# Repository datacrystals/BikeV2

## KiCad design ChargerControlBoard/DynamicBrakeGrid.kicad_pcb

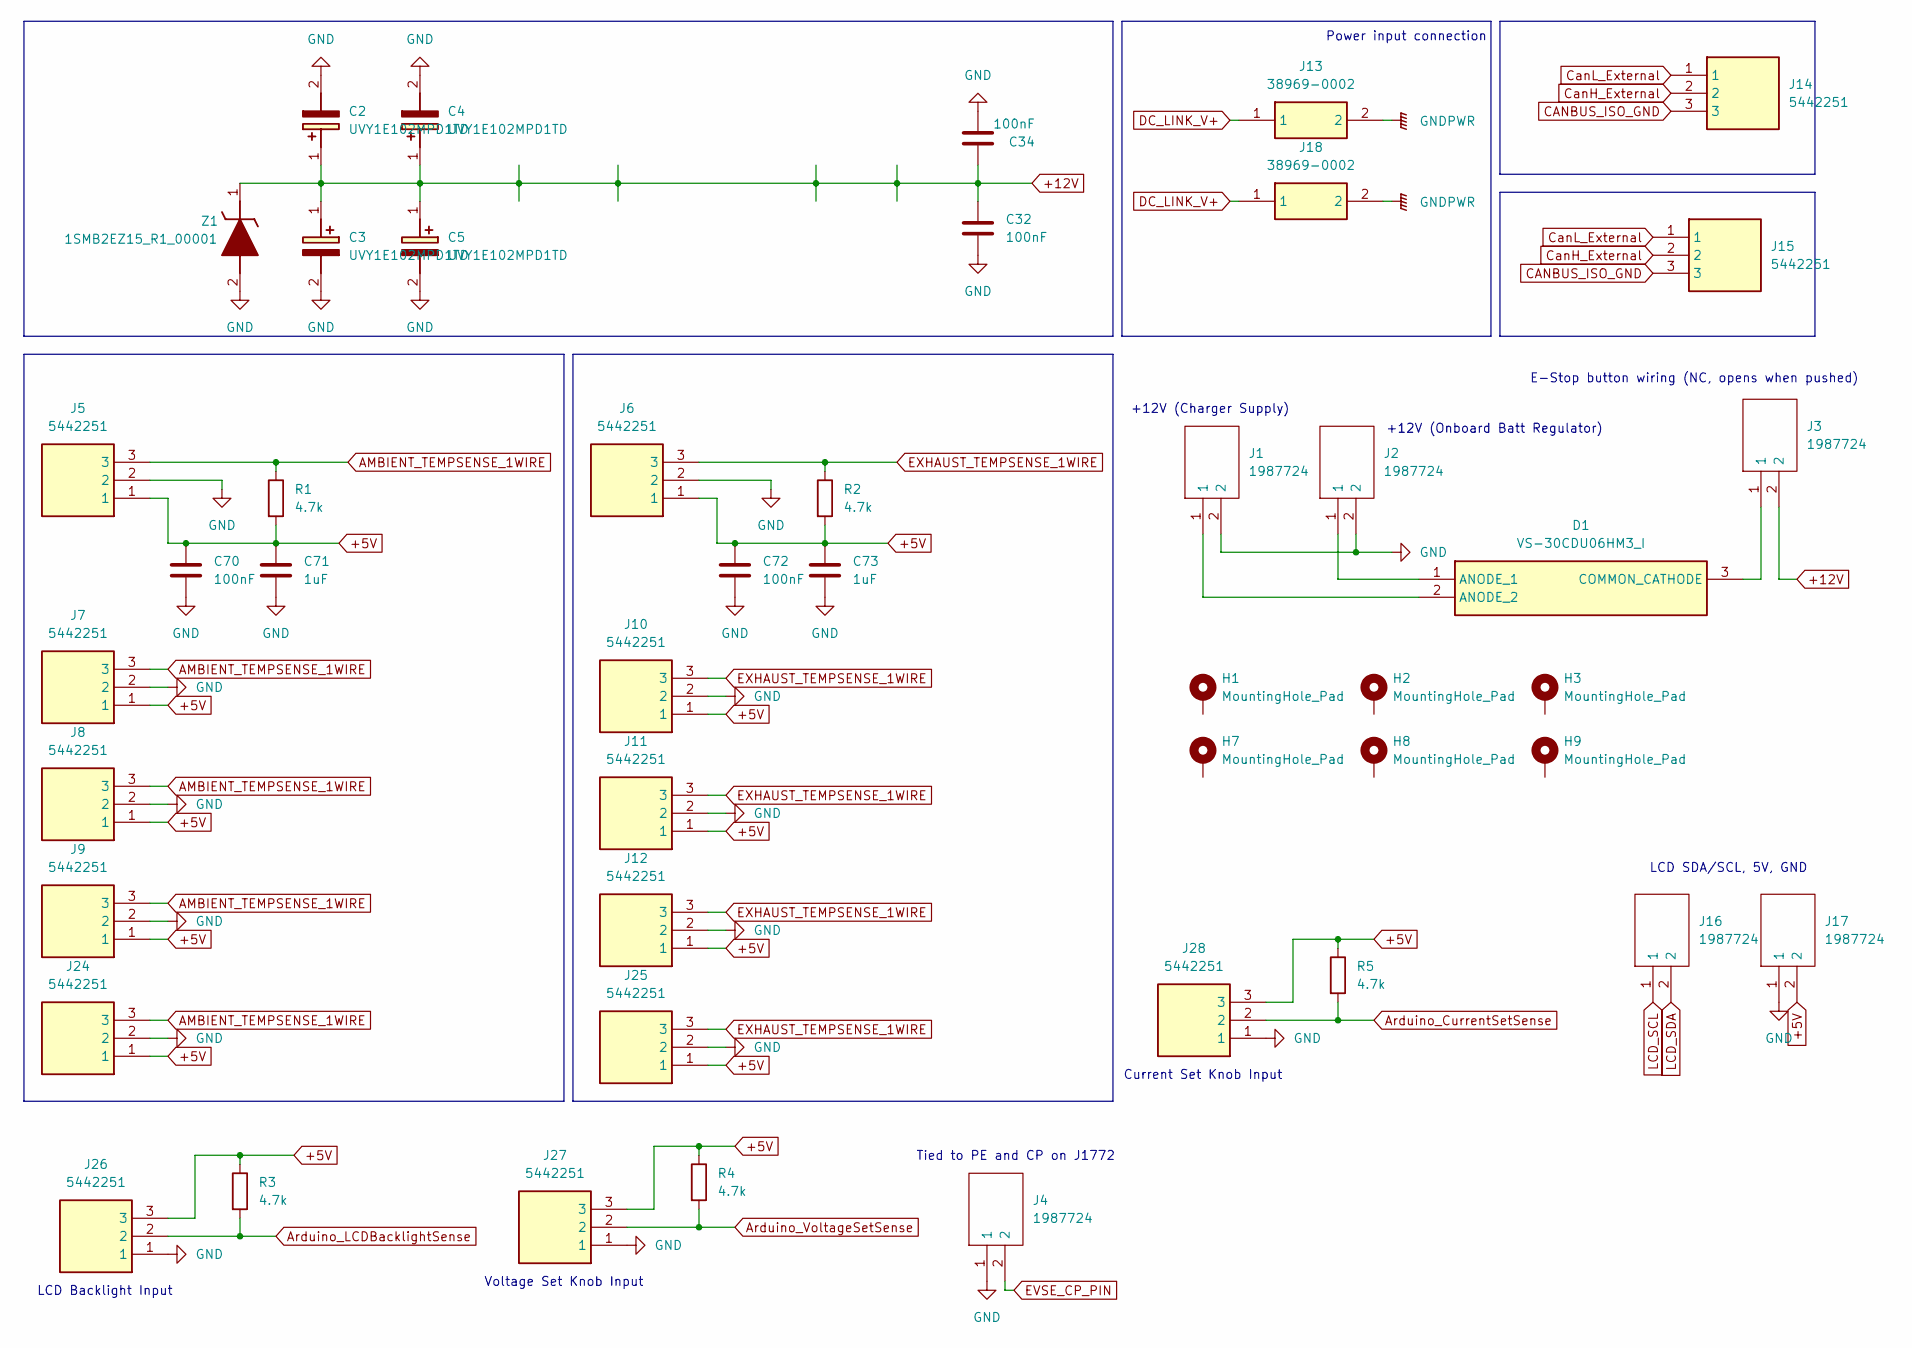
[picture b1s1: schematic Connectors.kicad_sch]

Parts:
C2, C3, C4, C5: UVY1E102MPD1TD; CAPPRD500W60D1025H1750; Mouser Part Number 647-UVY1E102MPD1TD
C32, C34, C70, C72: 100nF; C_1210_3225Metric_Pad1.33x2.70mm_HandSolder
C71, C73: 1uF; C_1210_3225Metric_Pad1.33x2.70mm_HandSolder
D1: VS-30CDU06HM3_I; VS30CDU06HM3I; Mouser Part Number 78-VS-30CDU06HM3I
H1, H2, H3, H7, H8, H9: MountingHole_Pad; MountingHole_5.3mm_M5_ISO7380_Pad
J1, J2, J3, J4, J16, J17: 1987724; Mouser Part Number 651-1987724
J5, J6, J7, J8, J9, J10, J11, J12, J14, J15, J24, J25, J26, J27, J28: 5442251; Mouser Part Number 651-5442251
J13, J18: 38969-0002; 389690002; Mouser Part Number 538-38969-0002
R1, R2, R3, R4, R5: 4.7k; R_1210_3225Metric_Pad1.30x2.65mm_HandSolder
Z1: 1SMB2EZ15_R1_00001; Mouser Part Number 241-1SMB2EZ15R100001

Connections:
+5V: C70.1, C71.1, C72.1, C73.1, J5.1, J6.1, J7.1, J8.1, J9.1, J10.1, J11.1, J12.1, J17.2, J24.1, J25.1, J26.3, J27.3, J28.3, R1.2, R2.2, R3.1, R4.1, R5.1; also elsewhere on the board
+12V: C2.1 (+), C3.1 (+), C4.1 (+), C5.1 (+), C32.1, C34.1, J3.2, Z1.1 (K); also elsewhere on the board
AMBIENT_TEMPSENSE_1WIRE: J5.3, J7.3, J8.3, J9.3, J24.3, R1.1; also elsewhere on the board
Arduino_CurrentSetSense: J28.2, R5.2; also elsewhere on the board
Arduino_LCDBacklightSense: J26.2, R3.2; also elsewhere on the board
Arduino_VoltageSetSense: J27.2, R4.2; also elsewhere on the board
CANBUS_ISO_GND: J14.3, J15.3; also elsewhere on the board
CanH_External: J14.2, J15.2; also elsewhere on the board
CanL_External: J14.1, J15.1; also elsewhere on the board
DC_LINK_V+: J13.1, J18.1; also elsewhere on the board
EVSE_CP_PIN: J4.2; also elsewhere on the board
EXHAUST_TEMPSENSE_1WIRE: J6.3, J10.3, J11.3, J12.3, J25.3, R2.1; also elsewhere on the board
GND: C2.2 (-), C3.2 (-), C4.2 (-), C5.2 (-), C32.2, C34.2, C70.2, C71.2, C72.2, C73.2, J1.2, J2.2, J4.1, J5.2, J6.2, J7.2, J8.2, J9.2, J10.2, J11.2, J12.2, J13.2, J17.1, J18.2, J24.2, J25.2, J26.1, J27.1, J28.1, Z1.2 (A); also elsewhere on the board
LCD_SCL: J16.1; also elsewhere on the board
LCD_SDA: J16.2; also elsewhere on the board
unnamed: D1.1 (ANODE_1), J2.1
unnamed: D1.2 (ANODE_2), J1.1
unnamed: D1.3 (COMMON_CATHODE), J3.1

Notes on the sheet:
E-Stop button wiring (NC, opens when pushed)
LCD Backlight Input
Voltage Set Knob Input
LCD SDA/SCL, 5V, GND
+12V (Onboard Batt Regulator)
+12V (Charger Supply)
Tied to PE and CP on J1772
Current Set Knob Input
Power input connection

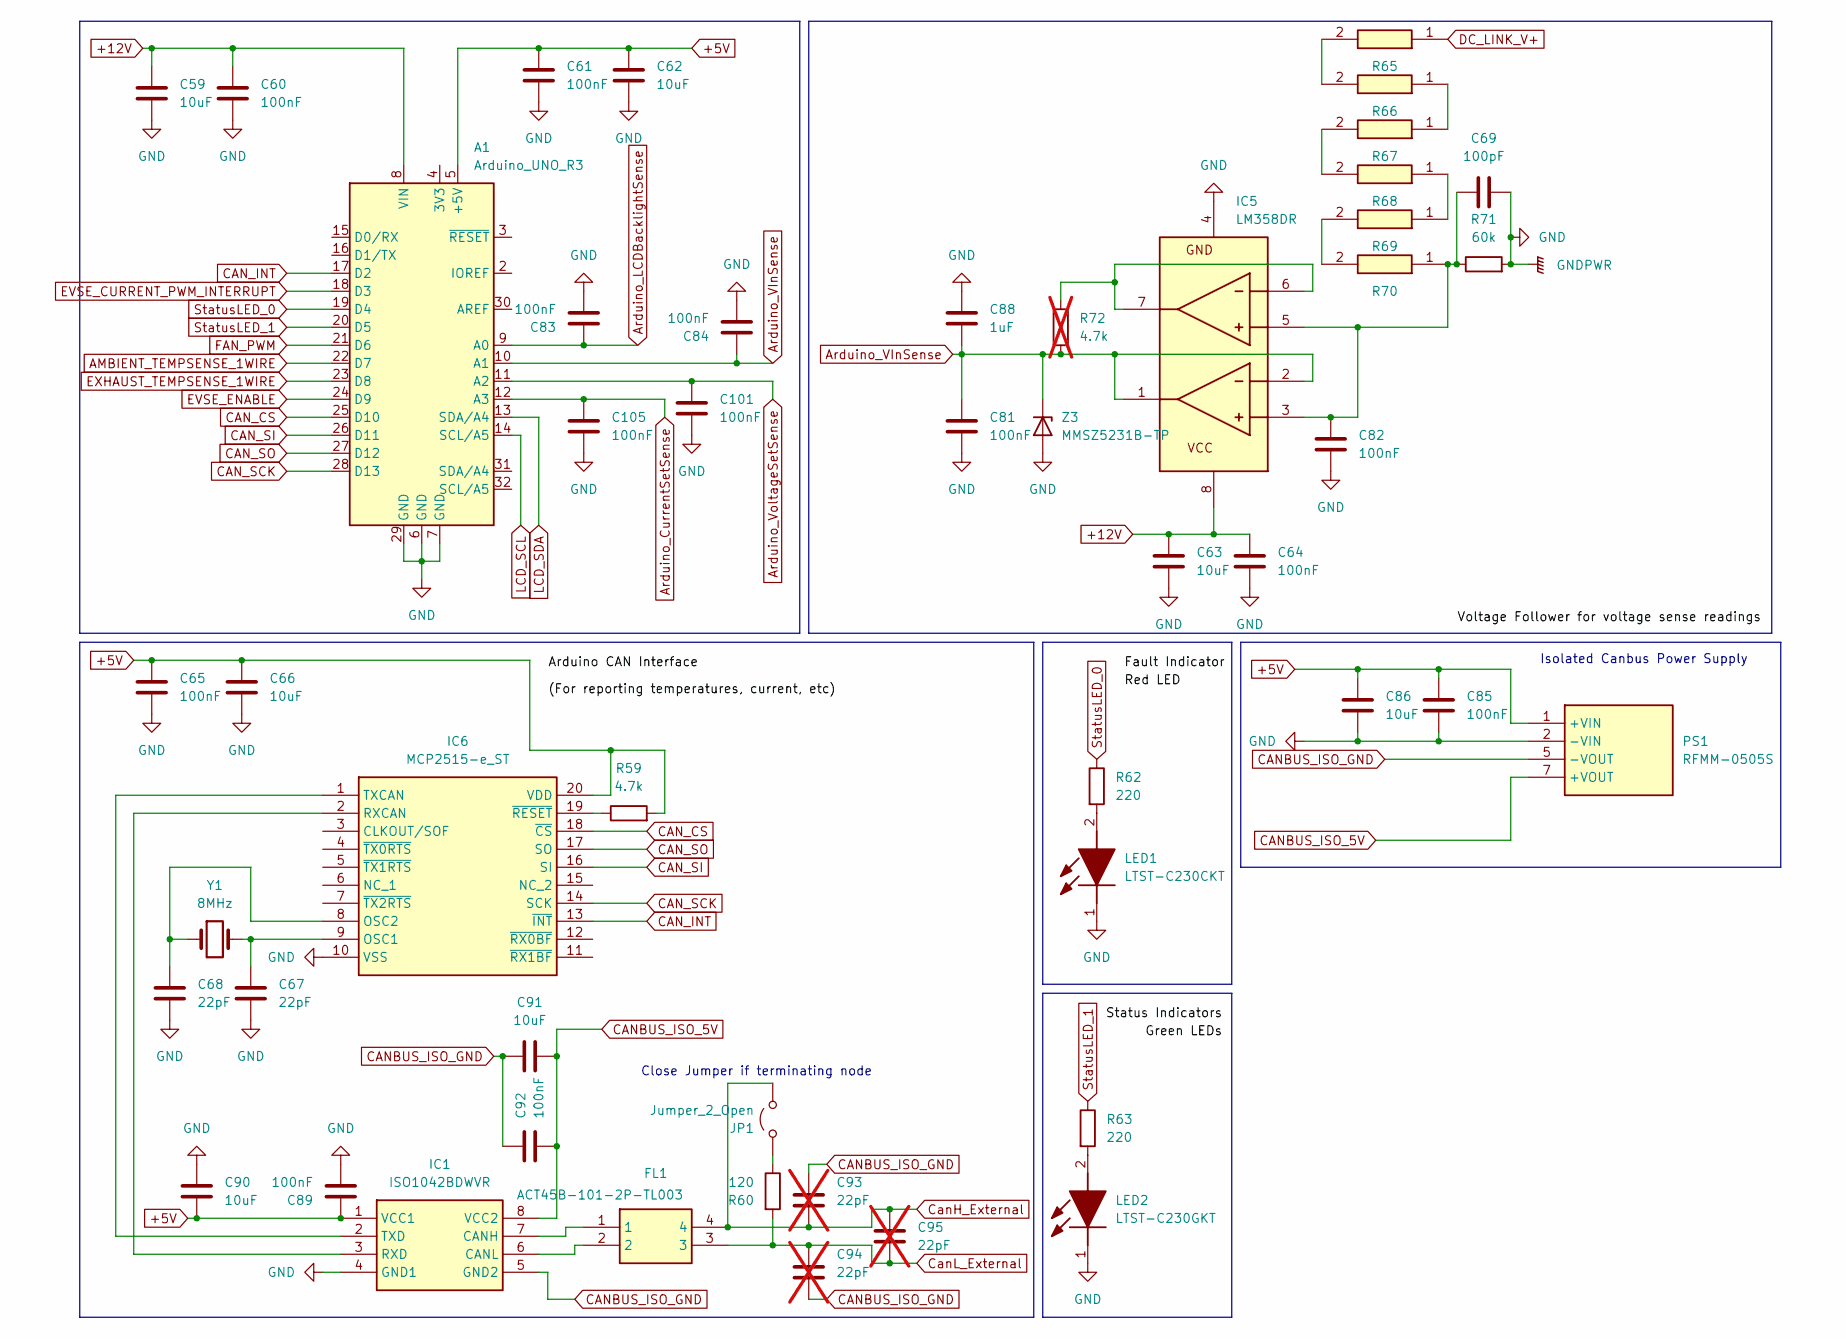
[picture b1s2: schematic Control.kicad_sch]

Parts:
A1: Arduino_UNO_R3; Arduino_UNO_R3_ModifiedCourtyard
C59, C62, C63, C66, C86, C90, C91: 10uF; C_1210_3225Metric_Pad1.33x2.70mm_HandSolder
C60, C61, C64, C65, C81, C82, C83, C84, C85, C89, C92, C101, C105: 100nF; C_1210_3225Metric_Pad1.33x2.70mm_HandSolder
C67, C68: 22pF; C_1210_3225Metric_Pad1.33x2.70mm_HandSolder
C69: 100pF; C_1210_3225Metric_Pad1.33x2.70mm_HandSolder
C88: 1uF; C_1210_3225Metric_Pad1.33x2.70mm_HandSolder
C93, C94, C95: 22pF; C_1210_3225Metric_Pad1.33x2.70mm_HandSolder; not fitted
FL1: ACT45B-101-2P-TL003; ACT45B1012PTL003; Mouser Part Number 810-ACT45B1012PTL003
IC1: ISO1042BDWVR; SOIC127P1150X280-8N; Mouser Part Number 595-ISO1042BDWVR
IC5: LM358DR; SOIC127P600X175-8N; Mouser Part Number 595-LM358DR
IC6: MCP2515-e_ST; SOP65P640X120-20N; Mouser Part Number 579-MCP2515-E/ST
JP1: Jumper_2_Open; PinHeader_1x02_P2.54mm_Vertical
LED1: LTST-C230CKT; LEDC3216X120N; Mouser Part Number 859-LTST-C230CKT
LED2: LTST-C230GKT; LEDC3216X120N; Mouser Part Number 859-LTST-C230GKT
PS1: RFMM-0505S; RFMM0505S; Mouser Part Number 919-RFMM-0505S
R59: 4.7k; R_1210_3225Metric_Pad1.30x2.65mm_HandSolder
R60: 120; R_1210_3225Metric_Pad1.30x2.65mm_HandSolder
R62, R63: 220; R_1210_3225Metric_Pad1.30x2.65mm_HandSolder
R65, R66, R67, R68, R69, R70: RC2512JK-071ML; RESC6431X65N; Mouser Part Number 603-RC2512JK-071ML
R71: 60k; R_1210_3225Metric_Pad1.30x2.65mm_HandSolder
R72: 4.7k; R_1210_3225Metric_Pad1.30x2.65mm_HandSolder; not fitted
Y1: 8MHz; Crystal_HC49-4H_Vertical
Z3: MMSZ5231B-TP; SOD3716X135N; Mouser Part Number 833-MMSZ5231B-TP

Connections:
+5V: A1.5 (+5V), C61.1, C62.1, C65.1, C66.1, C85.1, C86.1, C89.1, C90.2, IC1.1 (VCC1), IC6.20 (VDD), PS1.1 (+VIN), R59.2; also elsewhere on the board
+12V: A1.8 (VIN), C59.1, C60.1, C63.1, C64.1, IC5.8 (V+); also elsewhere on the board
AMBIENT_TEMPSENSE_1WIRE: A1.22 (D7); also elsewhere on the board
Arduino_CurrentSetSense: A1.12 (A3), C105.1; also elsewhere on the board
Arduino_LCDBacklightSense: A1.9 (A0), C83.1; also elsewhere on the board
Arduino_VInSense: A1.10 (A1), C81.1, C84.1, C88.2, IC5.1 (OUT1), IC5.2 (IN1-), R72.1, Z3.1 (K)
Arduino_VoltageSetSense: A1.11 (A2), C101.1; also elsewhere on the board
CANBUS_ISO_5V: C91.1, C92.2, IC1.8 (VCC2), PS1.7 (+VOUT)
CANBUS_ISO_GND: C91.2, C92.1, C93.1, C94.2, IC1.5 (GND2), PS1.5 (-VOUT); also elsewhere on the board
CAN_CS: A1.25 (D10), IC6.18 (~CS)
CAN_INT: A1.17 (D2), IC6.13 (~INT)
CAN_SCK: A1.28 (D13), IC6.14 (SCK)
CAN_SI: A1.26 (D11), IC6.16 (SI)
CAN_SO: A1.27 (D12), IC6.17 (SO)
CanH_External: C93.2, C95.1, FL1.4, JP1.2 (B); also elsewhere on the board
CanL_External: C94.1, C95.2, FL1.3, R60.2; also elsewhere on the board
DC_LINK_V+: R65.1; also elsewhere on the board
EVSE_CURRENT_PWM_INTERRUPT: A1.18 (D3); also elsewhere on the board
EVSE_ENABLE: A1.24 (D9); also elsewhere on the board
EXHAUST_TEMPSENSE_1WIRE: A1.23 (D8); also elsewhere on the board
FAN_PWM: A1.21 (D6); also elsewhere on the board
GND: A1.6 (GND), A1.7 (GND), A1.29 (GND), C59.2, C60.2, C61.2, C62.2, C63.2, C64.2, C65.2, C66.2, C67.2, C68.2, C69.2, C81.2, C82.2, C83.2, C84.2, C85.2, C86.2, C88.1, C89.2, C90.1, C101.2, C105.2, IC1.4 (GND1), IC5.4 (V-), IC6.10 (VSS), LED1.1 (K), LED2.1 (K), PS1.2 (-VIN), R71.2, Z3.2 (A); also elsewhere on the board
LCD_SCL: A1.14 (SCL/A5); also elsewhere on the board
LCD_SDA: A1.13 (SDA/A4); also elsewhere on the board
unnamed: FL1.1, IC1.7 (CANH)
unnamed: FL1.2, IC1.6 (CANL)
unnamed: IC1.3 (RXD), IC6.2 (RXCAN)
unnamed: IC1.2 (TXD), IC6.1 (TXCAN)
unnamed: C69.1, C82.1, IC5.3 (IN1+), IC5.5 (IN2+), R70.1, R71.1
unnamed: IC5.6 (IN2-), IC5.7 (OUT2), R72.2
unnamed: C67.1, IC6.9 (OSC1), Y1.2
unnamed: C68.1, IC6.8 (OSC2), Y1.1
unnamed: IC6.19 (~RESET), R59.1
unnamed: JP1.1 (A), R60.1
unnamed: LED1.2 (A), R62.2
unnamed: LED2.2 (A), R63.2
unnamed: R65.2, R66.2
unnamed: R66.1, R67.1
unnamed: R67.2, R68.2
unnamed: R68.1, R69.1
unnamed: R69.2, R70.2
StatusLED_0: A1.19 (D4), R62.1
StatusLED_1: A1.20 (D5), R63.1

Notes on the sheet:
Close Jumper if terminating node
Isolated Canbus Power Supply

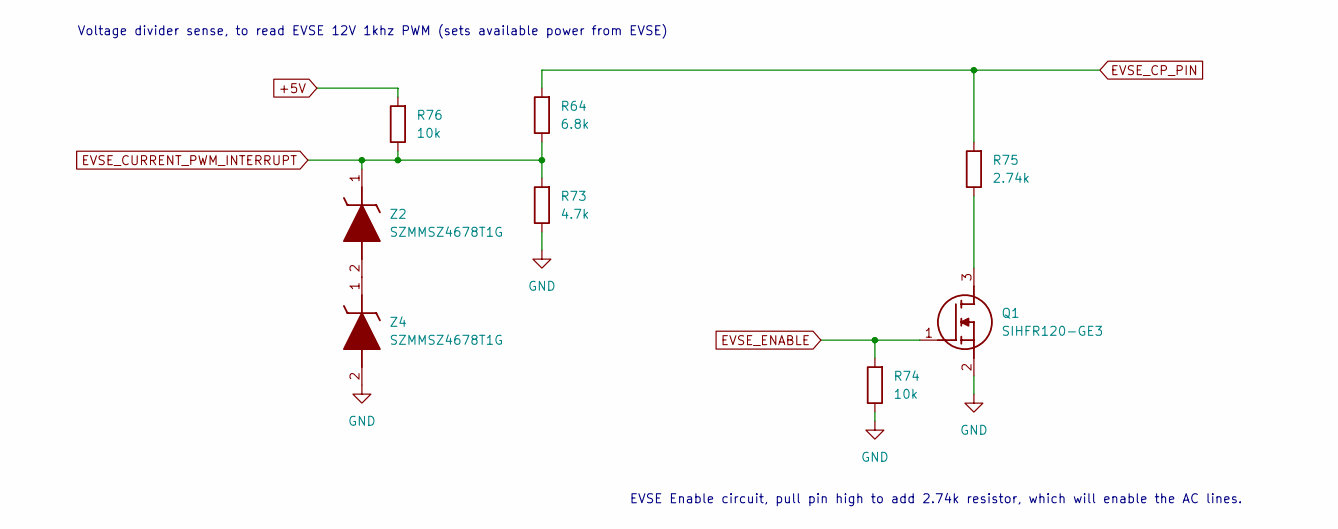
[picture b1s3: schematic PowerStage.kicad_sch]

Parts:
Q1: SIHFR120-GE3; SIHFR120GE3; Mouser Part Number 78-SIHFR120-GE3
R64: 6.8k; R_1210_3225Metric_Pad1.30x2.65mm_HandSolder
R73: 4.7k; R_1210_3225Metric_Pad1.30x2.65mm_HandSolder
R74, R76: 10k; R_1210_3225Metric_Pad1.30x2.65mm_HandSolder
R75: 2.74k; R_1210_3225Metric_Pad1.30x2.65mm_HandSolder
Z2, Z4: SZMMSZ4678T1G; SOD3716X135N; Mouser Part Number 863-SZMMSZ4678T1G

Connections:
+5V: R76.2; also elsewhere on the board
EVSE_CP_PIN: R64.2, R75.2; also elsewhere on the board
EVSE_CURRENT_PWM_INTERRUPT: R64.1, R73.2, R76.1, Z2.1 (K); also elsewhere on the board
EVSE_ENABLE: Q1.1 (G), R74.2; also elsewhere on the board
GND: Q1.2 (S), R73.1, R74.1, Z4.2 (A); also elsewhere on the board
unnamed: Q1.3 (D), R75.1
unnamed: Z2.2 (A), Z4.1 (K)

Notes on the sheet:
Voltage divider sense, to read EVSE 12V 1khz PWM (sets available power from EVSE)
EVSE Enable circuit, pull pin high to add 2.74k resistor, which will enable the AC lines.

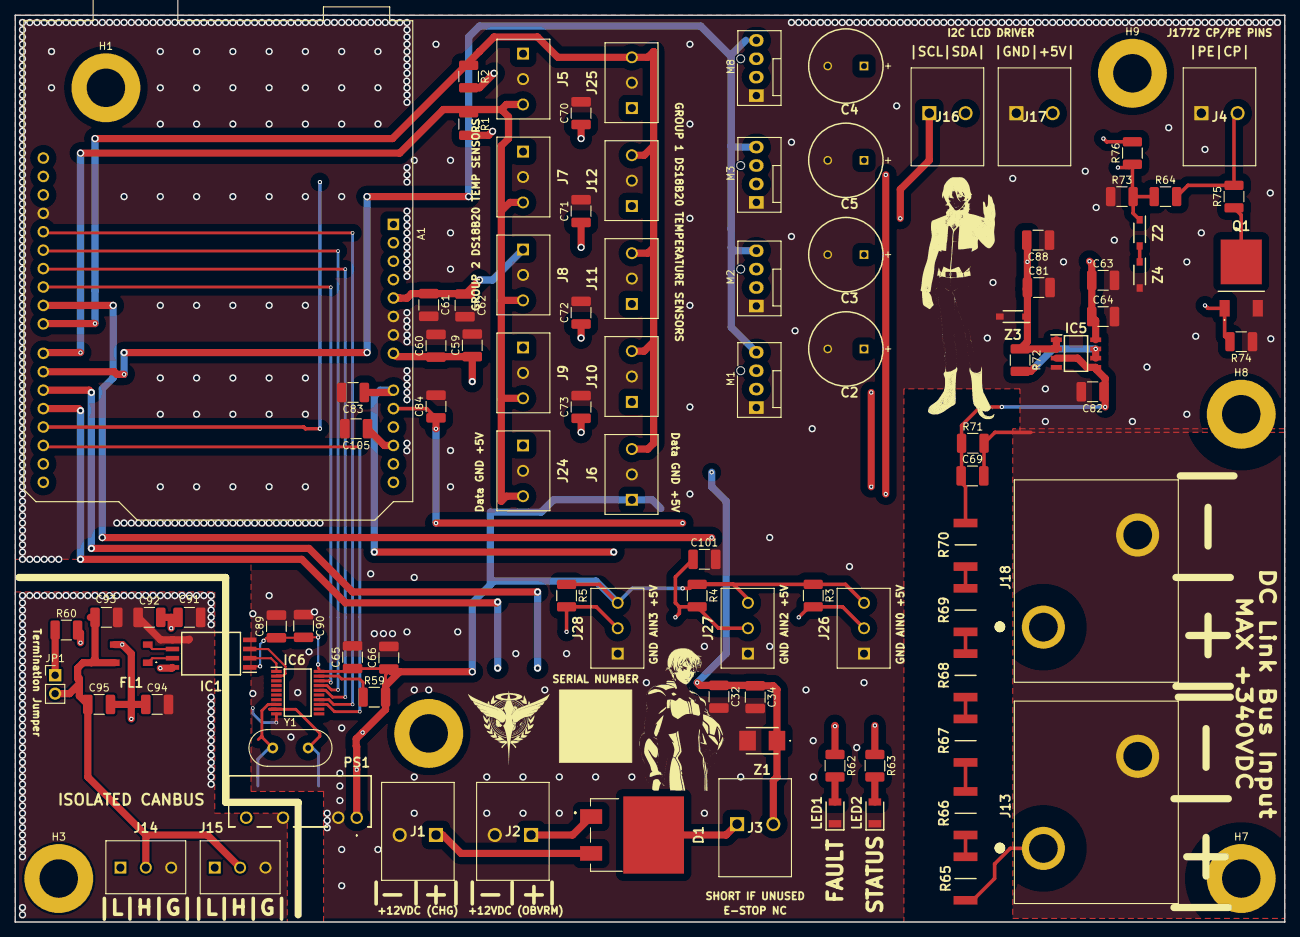
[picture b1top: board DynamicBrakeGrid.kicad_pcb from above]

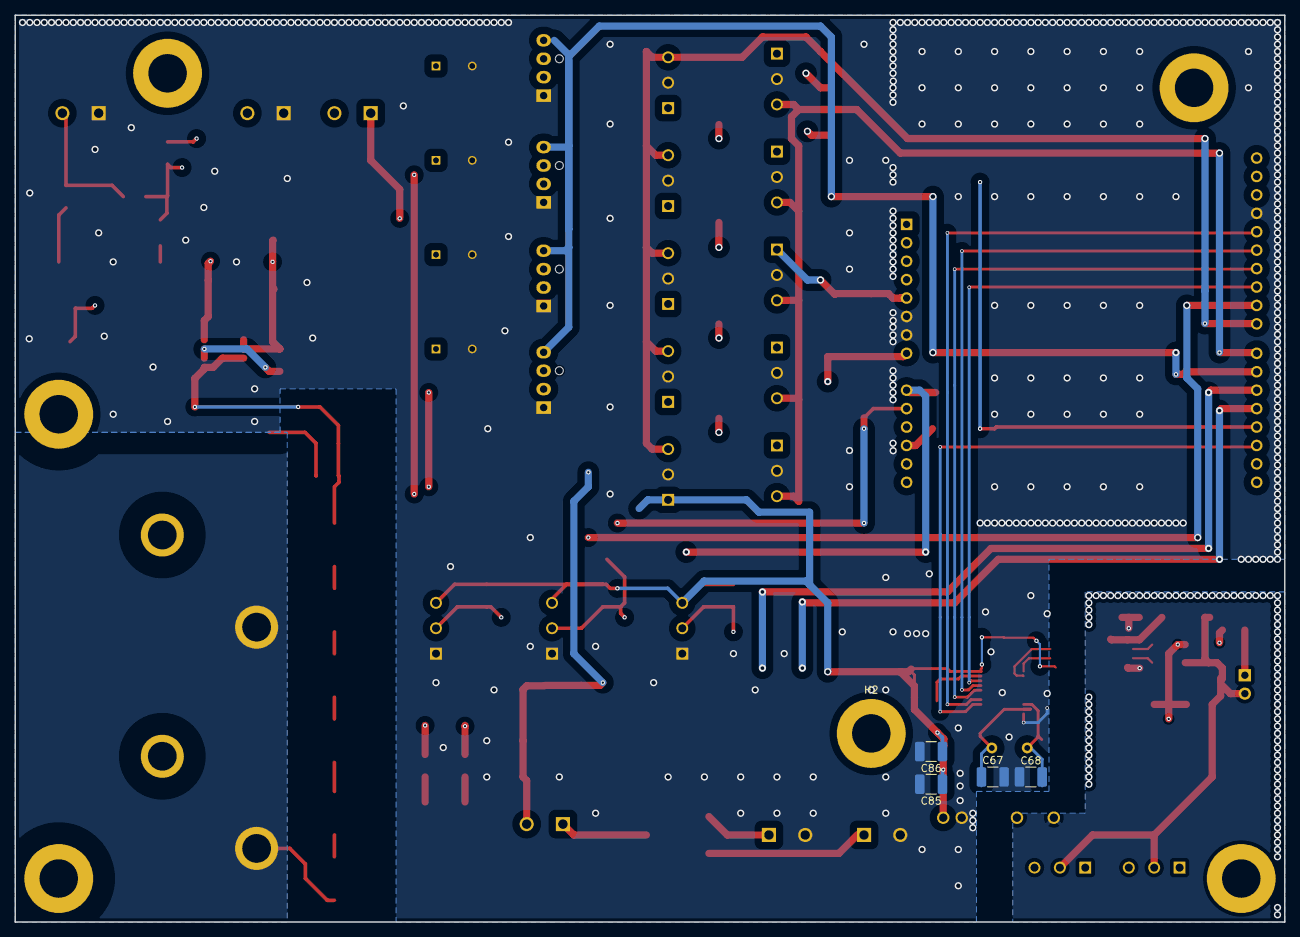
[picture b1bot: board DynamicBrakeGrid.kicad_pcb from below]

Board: 4 copper layers, 175.0 x 125.0 mm, 108 parts (4 on the bottom side), 49 nets.

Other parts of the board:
M1, M2, M3, M8: Fan_4pin; FanPinHeader_1x04_P2.54mm_Vertical

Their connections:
+12V: M1.2 (+), M2.2 (+), M3.2 (+), M8.2 (+); also elsewhere on the board
FAN_PWM: M1.4 (PWM), M2.4 (PWM), M3.4 (PWM), M8.4 (PWM); also elsewhere on the board
GND: M1.1 (-), M2.1 (-), M3.1 (-), M8.1 (-); also elsewhere on the board

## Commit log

2025-05-10 Add Initial Parts
2025-05-11 Add Headlight Mount
2025-05-11 Add Tail Light
2025-05-13 Design Improvements
2025-05-13 Update Gcode
2025-06-06 Update Bike Parts
2025-06-15 Update enclosure
2025-06-15 Add Fab data
2025-06-16 Redesign Battery Enclosure
2025-06-25 Update bike mounting plate
2025-06-27 Update Enclosures
2025-06-27 Add Wiring Enclosure
2025-06-27 Bottom battery Mount V2
2025-06-27 Enclosure Updates
2025-07-02 Add Start Of Canbus Board For Charger
2025-07-06 Add Charger Control Board (half done)
2025-07-08 Finish Layout On Control Board
2025-07-08 Update OBC Board
2025-07-10 Update Bike Mounting Structure
2025-07-10 Add Charger Mount Plate
2025-07-16 Add Mounting Holes
2025-07-24 Add V1 Firmware
2025-07-29 update fw
